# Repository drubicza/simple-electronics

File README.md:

# simple-electronics

Simple project mostly using discrete components from around the web.

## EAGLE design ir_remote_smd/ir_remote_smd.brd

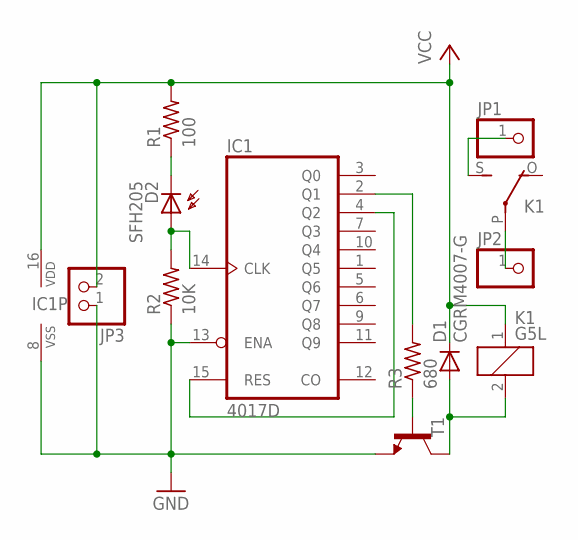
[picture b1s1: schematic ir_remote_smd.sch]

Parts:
D1: CGRM4007-G; SOD-123_MINI-SMA
D2: SFH205
IC1: 4017D; SO16
JP1, JP2: PINHD-1X1; 1X01
JP3: PINHD-1X2; 1X02
K1: G5L; G5LE
R1: 100; R0603
R2: 10K; R0603
R3: 680; R0603
T1: MMBT2222ALT1-NPN-SOT23-BEC; SOT23-BEC

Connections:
GND: IC1.8 (VSS), IC1.13 (ENA), JP3.1, R2.1, T1.E
unnamed: IC1.4 (Q2), IC1.15 (RES)
unnamed: IC1.2 (Q1), R3.2
unnamed: R3.1, T1.B
unnamed: D2.A, IC1.14 (CLK), R2.2
unnamed: D2.K (C), R1.1
PWR_IN: JP2.1, K1.P
PWR_OUT: JP1.1, K1.S
REL_SIG: D1.A, K1.2, T1.C
VCC: D1.C, IC1.16 (VDD), JP3.2, K1.1, R1.2

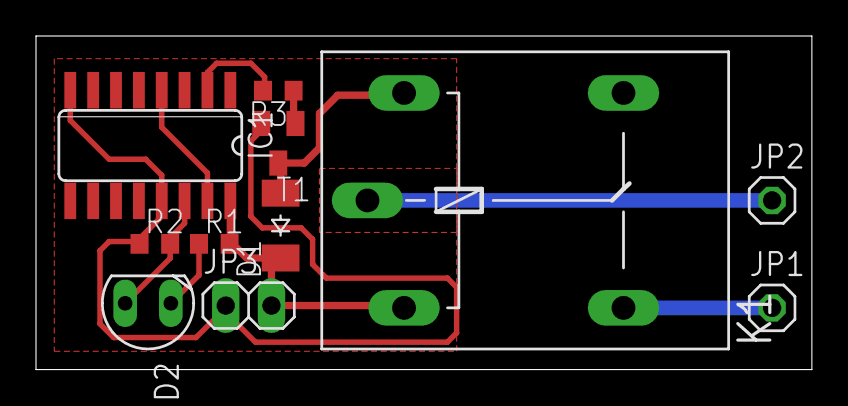
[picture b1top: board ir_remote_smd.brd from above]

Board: 2 copper layers, 43.1 x 18.5 mm, 11 parts (0 on the bottom side), 10 nets.
